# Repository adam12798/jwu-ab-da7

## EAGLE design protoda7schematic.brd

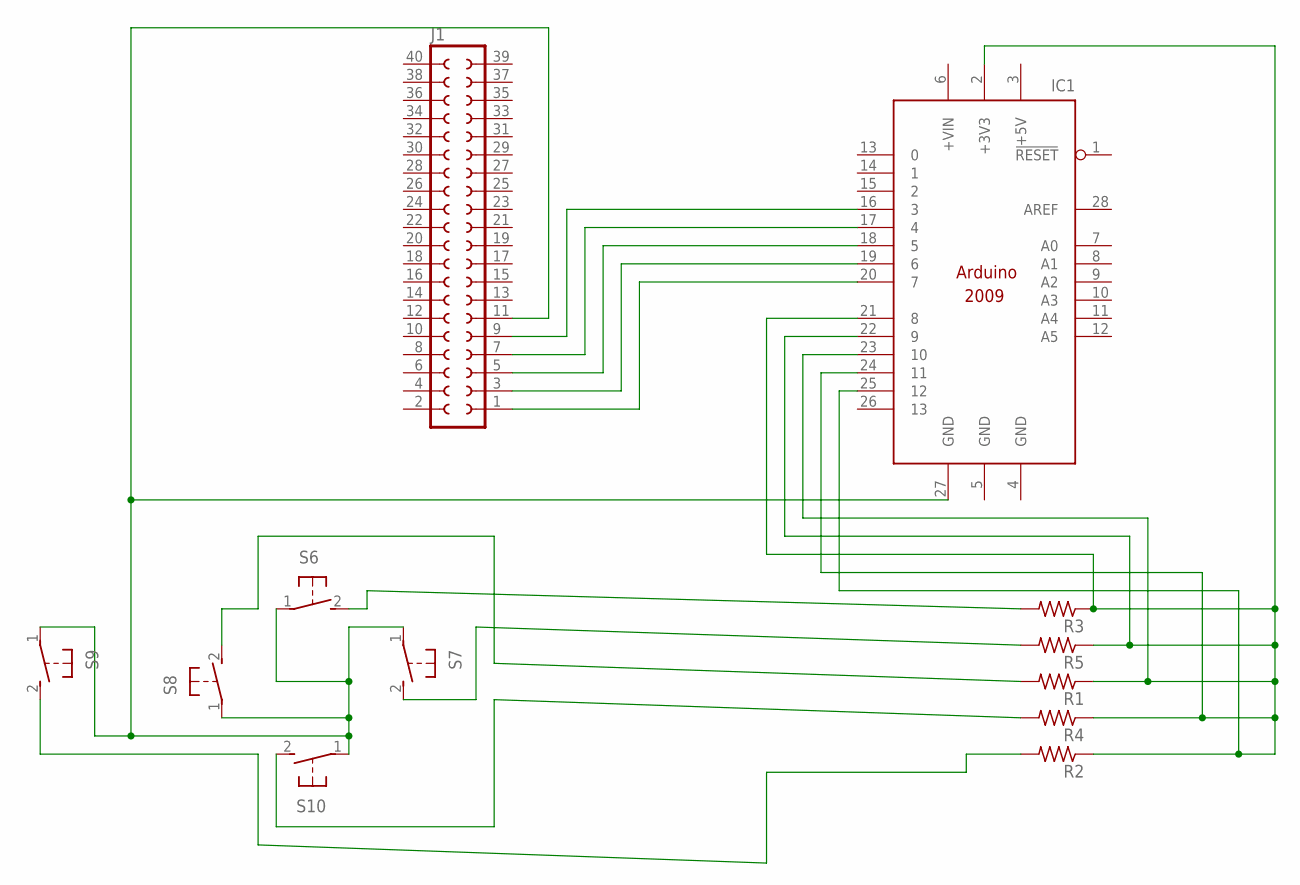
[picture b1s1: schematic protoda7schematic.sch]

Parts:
IC1: ARDUINO2009_10; ARDUINO2009
J1: SOCKET-40V; S40V
R1, R2, R3, R4, R5: R-US_0204/5; 0204/5
S6, S7, S8, S9, S10: 31-XX; B3F-31XX

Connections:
+5V: IC1.3 (+5V)
GND: IC1.4 (GND), IC1.5 (GND)
unnamed: IC1.20 (7), J1.1
unnamed: IC1.19 (6), J1.3
unnamed: IC1.18 (5), J1.5
unnamed: IC1.17 (4), J1.7
unnamed: IC1.16 (3), J1.9
unnamed: IC1.2 (+3V3), IC1.21 (8), IC1.22 (9), IC1.23 (10), IC1.24 (11), IC1.25 (12), R1.1, R2.1, R3.1, R4.1, R5.1
unnamed: R3.2, S6.2 (S)
unnamed: R5.2, S7.2 (S)
unnamed: IC1.27 (GND), J1.11, S6.1, S7.1, S8.1, S9.1, S10.1
unnamed: R4.2, S10.2 (S)
unnamed: R1.2, S8.2 (S)
unnamed: R2.2, S9.2 (S)

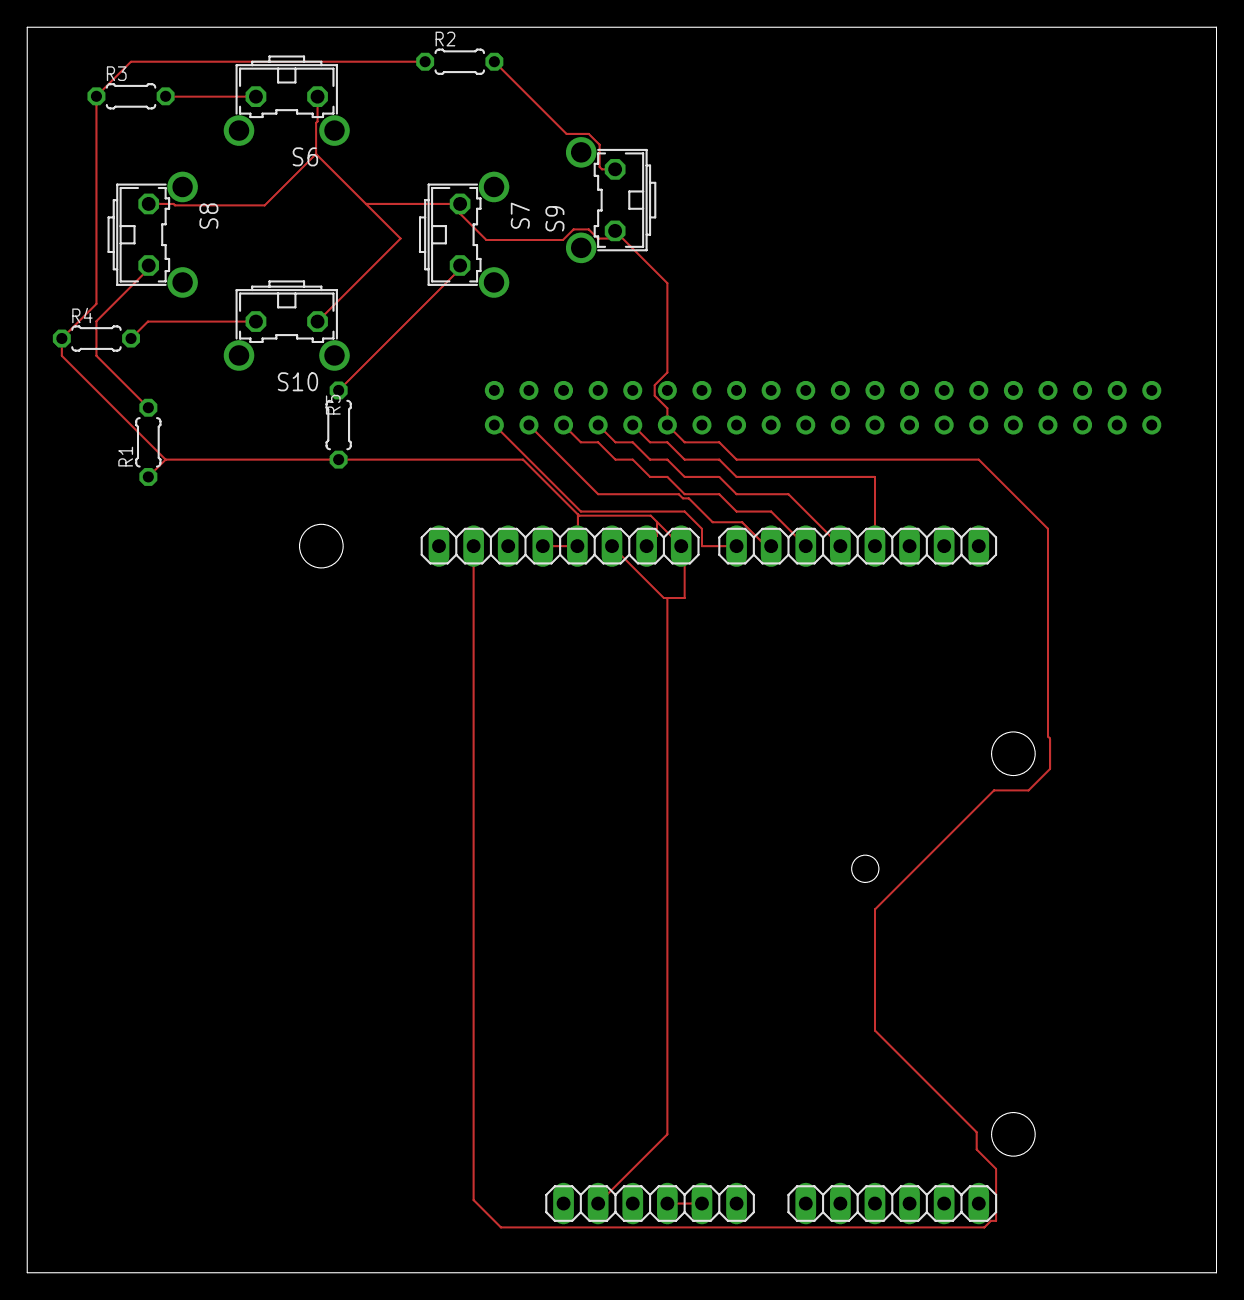
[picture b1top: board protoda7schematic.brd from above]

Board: 2 copper layers, 87.3 x 91.4 mm, 12 parts (1 on the bottom side), 13 nets.
